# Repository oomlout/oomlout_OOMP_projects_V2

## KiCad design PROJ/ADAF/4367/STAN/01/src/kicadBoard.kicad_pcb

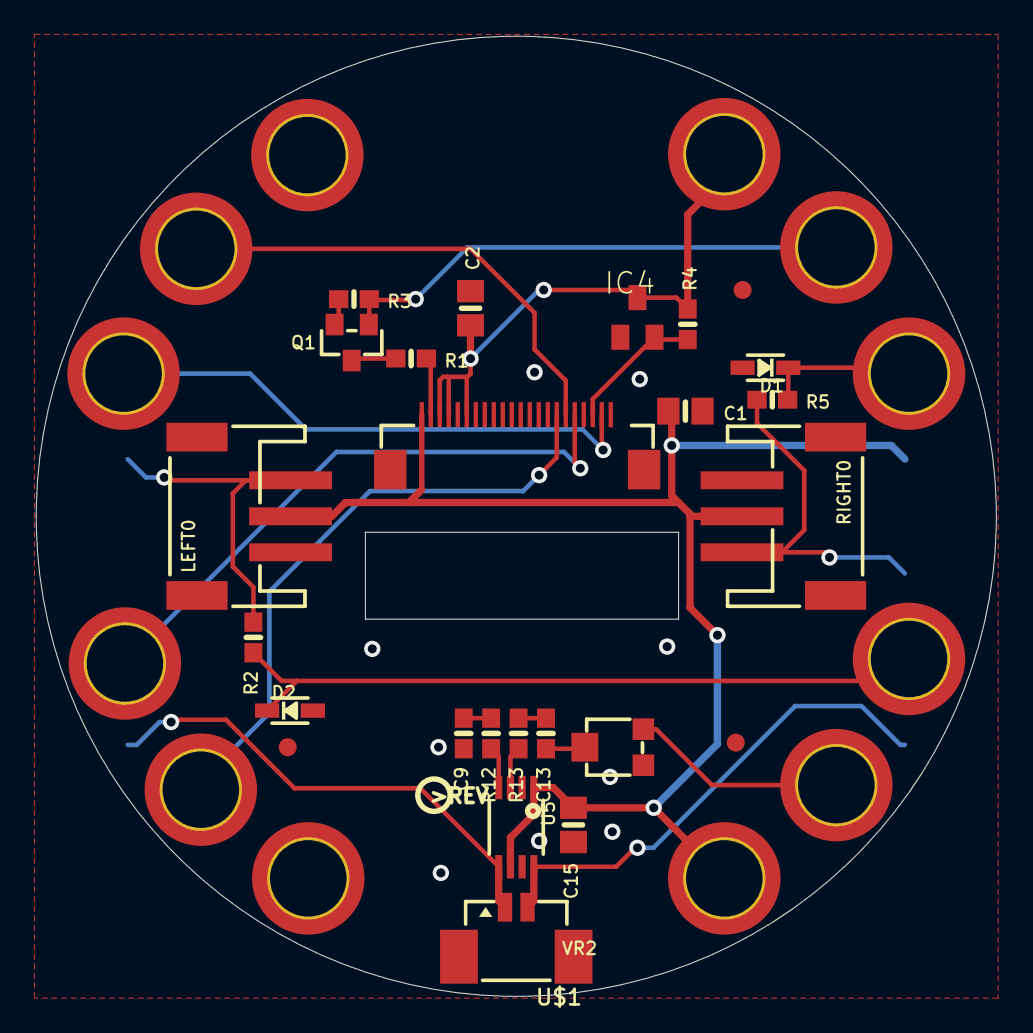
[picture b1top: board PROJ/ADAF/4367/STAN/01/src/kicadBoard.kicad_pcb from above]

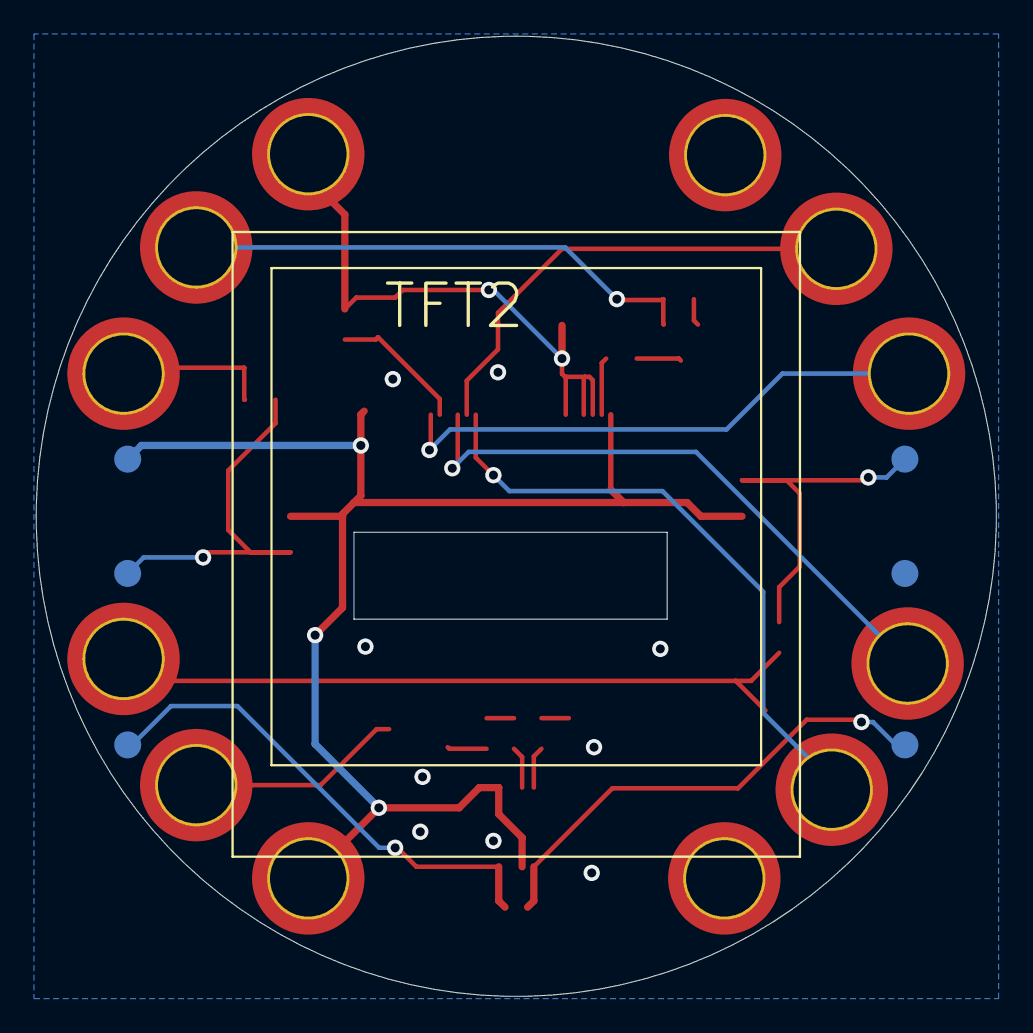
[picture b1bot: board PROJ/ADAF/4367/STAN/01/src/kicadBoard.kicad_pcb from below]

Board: 16 copper layers, 53.3 x 53.3 mm, 46 parts (8 on the bottom side), 23 nets.

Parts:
C1, C2, C15: 10uF; 0805-NO
C9, C13: 1uF; 0603-NO
D1, D2: 3.6V; SOD-323
IC4: APX803-SAG; SOT23
LEFT0: JST PH 3; JSTPH3
Q1: BSS138; SOT23-WIDE
R1: 33 ohm; 0603-NO
R2, R5: 1K; 0603-NO
R3, R4: 10K; 0603-NO
R12, R13: 100; 0603-NO
RIGHT0: JST PH 3; JSTPH3
TFT2: DISP_TFT_1.54IN_240X240_22P; TFT_1.54IN_240X240_22PIN
TP1, TP14, TP15, TP16, TP17, TP18: TESTPOINT_ROUND_1.5MM_NO
TP2, TP3, TP4, TP5, TP6, TP7, TP8, TP9, TP10, TP11, TP12, TP13: SEWTAP_SMTNUTM3; SMT_NUT_3MM
U5: PAM8302AASCR; MSOP8_0.65MM
U$1: CON_MOLEX_2P; 53398-0271
U$2, U$3, U$6: FIDUCIAL_1MM
U$7: PCBFEAT-REV-040
U$17: TFTGIZMO_FRONT
U$18: TFTGIZMO_BACK
VR2: 10K trim; TRIMPOT_BOURNS_3303W

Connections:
3.3V: C2.1, IC4.3, R4.2, TFT2.3, TFT2.4, TFT2.6, TP2.P$1
A0_SPEAKER: TP9.P$1, VR2.3
A1: D2.C, R2.2, TP8.P$1
A1_: LEFT0.3, R2.1, TP1.P$1
A2: D1.C, R5.2, TP7.P$1
A2_: R5.1, RIGHT0.3, TP14.P$1
A3_BACKLITE: Q1.1, R3.2, TP6.P$1
A6_CS: TFT2.18, TP12.P$1
A7_DC: TFT2.16, TP13.P$1
GND: C1.2, C2.2, C9.2, C15.2, D1.A, D2.A, IC4.1, LEFT0.1, Q1.2, R3.1, RIGHT0.1, TFT2.5, TFT2.7, TFT2.8, TFT2.9, TFT2.10, TFT2.11, TFT2.12, TFT2.13, TFT2.14, TFT2.15, TFT2.22, TFT2.SUPPORT1, TFT2.SUPPORT2, TP4.P$1, TP5.P$1, TP18.P$1, U5.7, VR2.1
LEDK: R1.2, TFT2.2
MOSI: TFT2.21, TP11.P$1
unnamed: Q1.3, R1.1
unnamed: R12.2, U5.4
unnamed: R13.2, U5.3
unnamed: C9.1, R12.1
unnamed: C13.1, R13.1
unnamed: C13.2, VR2.2
SCK: TFT2.17, TP10.P$1
SPKR+: TP15.P$1, U5.5, U$1.1
SPKR-: TP16.P$1, U5.8, U$1.2
V+: C1.1, C15.1, LEFT0.2, RIGHT0.2, TFT2.1, TP3.P$1, TP17.P$1, U5.1, U5.6
~TFT_RST: IC4.2, R4.1, TFT2.20

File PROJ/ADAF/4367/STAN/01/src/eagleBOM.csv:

"Part";"Value";"Device";"Package";"Description";"BOM";
"C1";"10uF";"CAP_CERAMIC0805-NOOUTLINE";"0805-NO";"Ceramic Capacitors";"";
"C2";"10uF";"CAP_CERAMIC0805-NOOUTLINE";"0805-NO";"Ceramic Capacitors";"";
"C9";"1uF";"CAP_CERAMIC0603_NO";"0603-NO";"Ceramic Capacitors";"";
"C13";"1uF";"CAP_CERAMIC0603_NO";"0603-NO";"Ceramic Capacitors";"";
"C15";"10uF";"CAP_CERAMIC0805-NOOUTLINE";"0805-NO";"Ceramic Capacitors";"";
"D1";"3.6V";"DIODE-ZENERSOD323";"SOD-323";"Zener Diode";"";
"D2";"3.6V";"DIODE-ZENERSOD323";"SOD-323";"Zener Diode";"";
"IC4";"APX803-SAG";"AXP083-SAG";"SOT23";"";"";
"LEFT";"JST PH 3";"CON_JST_PH_3PIN";"JSTPH3";"";"";
"Q1";"BSS138";"MOSFET-NWIDE";"SOT23-WIDE";"N-Channel Mosfet";"";
"R1";"33 ohm";"RESISTOR_0603_NOOUT";"0603-NO";"Resistors";"";
"R2";"1K";"RESISTOR_0603_NOOUT";"0603-NO";"Resistors";"";
"R3";"10K";"RESISTOR_0603_NOOUT";"0603-NO";"Resistors";"";
"R4";"10K";"RESISTOR_0603_NOOUT";"0603-NO";"Resistors";"";
"R5";"1K";"RESISTOR_0603_NOOUT";"0603-NO";"Resistors";"";
"R12";"100";"RESISTOR_0603_NOOUT";"0603-NO";"Resistors";"";
"R13";"100";"RESISTOR_0603_NOOUT";"0603-NO";"Resistors";"";
"RIGHT";"JST PH 3";"CON_JST_PH_3PIN";"JSTPH3";"";"";
"TFT2";"DISP_TFT_1.54IN_240X240_22P";"DISP_TFT_1.54IN_240X240_22P";"TFT_1.54IN_240X240_22PIN";"";"";
"TP1";"";"TESTPOINTROUND1.5MMNO";"TESTPOINT_ROUND_1.5MM_NO";"Test Point";"";
"TP2";"SEWTAP_SMTNUTM3";"SEWTAP_SMTNUTM3";"SMT_NUT_3MM";"";"";
"TP3";"SEWTAP_SMTNUTM3";"SEWTAP_SMTNUTM3";"SMT_NUT_3MM";"";"";
"TP4";"SEWTAP_SMTNUTM3";"SEWTAP_SMTNUTM3";"SMT_NUT_3MM";"";"";
"TP5";"SEWTAP_SMTNUTM3";"SEWTAP_SMTNUTM3";"SMT_NUT_3MM";"";"";
"TP6";"SEWTAP_SMTNUTM3";"SEWTAP_SMTNUTM3";"SMT_NUT_3MM";"";"";
"TP7";"SEWTAP_SMTNUTM3";"SEWTAP_SMTNUTM3";"SMT_NUT_3MM";"";"";
"TP8";"SEWTAP_SMTNUTM3";"SEWTAP_SMTNUTM3";"SMT_NUT_3MM";"";"";
"TP9";"SEWTAP_SMTNUTM3";"SEWTAP_SMTNUTM3";"SMT_NUT_3MM";"";"";
"TP10";"SEWTAP_SMTNUTM3";"SEWTAP_SMTNUTM3";"SMT_NUT_3MM";"";"";
"TP11";"SEWTAP_SMTNUTM3";"SEWTAP_SMTNUTM3";"SMT_NUT_3MM";"";"";
"TP12";"SEWTAP_SMTNUTM3";"SEWTAP_SMTNUTM3";"SMT_NUT_3MM";"";"";
"TP13";"SEWTAP_SMTNUTM3";"SEWTAP_SMTNUTM3";"SMT_NUT_3MM";"";"";
"TP14";"";"TESTPOINTROUND1.5MMNO";"TESTPOINT_ROUND_1.5MM_NO";"Test Point";"";
"TP15";"";"TESTPOINTROUND1.5MMNO";"TESTPOINT_ROUND_1.5MM_NO";"Test Point";"";
"TP16";"";"TESTPOINTROUND1.5MMNO";"TESTPOINT_ROUND_1.5MM_NO";"Test Point";"";
"TP17";"";"TESTPOINTROUND1.5MMNO";"TESTPOINT_ROUND_1.5MM_NO";"Test Point";"";
"TP18";"";"TESTPOINTROUND1.5MMNO";"TESTPOINT_ROUND_1.5MM_NO";"Test Point";"";
"U$1";"CON_MOLEX_2P";"CON_MOLEX_2P";"53398-0271";"";"";
"U$2";"FIDUCIAL_1MM";"FIDUCIAL_1MM";"FIDUCIAL_1MM";"Fiducial Alignment Points";"EXCLUDE";
"U$3";"FIDUCIAL_1MM";"FIDUCIAL_1MM";"FIDUCIAL_1MM";"Fiducial Alignment Points";"EXCLUDE";
"U$6";"FIDUCIAL_1MM";"FIDUCIAL_1MM";"FIDUCIAL_1MM";"Fiducial Alignment Points";"EXCLUDE";
"U5";"PAM8302AASCR";"AUDIOAMP_PAM8302A";"MSOP8_0.65MM";"PAM8302A - 2.5W Class-D Mono Audio Amplifier";"";
"VR2";"10K trim";"TRIMPOT3303W/X";"TRIMPOT_BOURNS_3303W";"3-Pin SMT Trimpots";"";

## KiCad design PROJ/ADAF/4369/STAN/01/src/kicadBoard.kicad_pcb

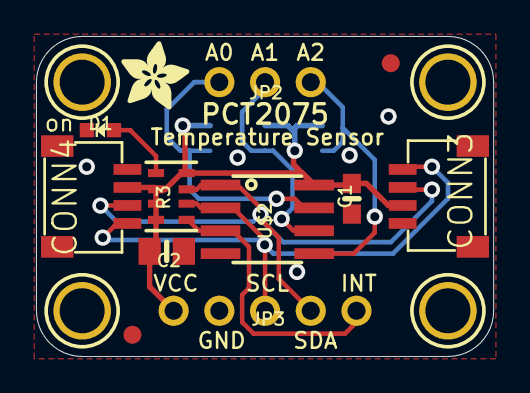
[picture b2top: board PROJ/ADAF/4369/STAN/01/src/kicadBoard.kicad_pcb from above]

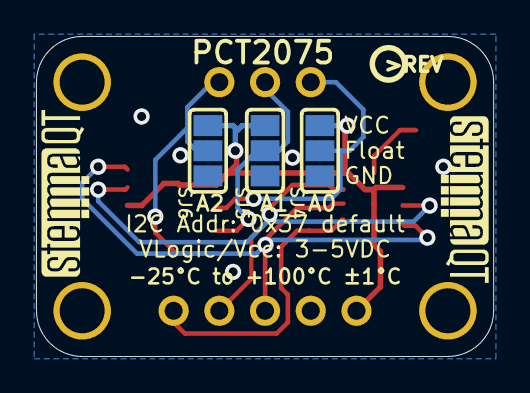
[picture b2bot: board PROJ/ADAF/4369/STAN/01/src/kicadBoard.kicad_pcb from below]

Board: 2 copper layers, 25.4 x 17.8 mm, 22 parts (6 on the bottom side), 9 nets.

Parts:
C1: 0.1uF; 0603-NO
C2: 10uF; 0805-NO
CONN3, CONN4: STEMMA_I2C_QT; JST_SH4
D1: GREEN; CHIPLED_0603_NOOUTLINE
FID3, FID4: FIDUCIAL_1MM
JP2: 1X03_ROUND
JP3: 1X05_ROUND
R3: 10K; RESPACK_4X0603
SJ4, SJ5, SJ6: SOLDERJUMPER_2WAY_OPEN_NOPASTE
U$1, U$17, U$19, U$21: MOUNTINGHOLE2.5; MOUNTINGHOLE_2.5_PLATED
U$2: PCT2075D; SOIC8_150MIL
U$22: ADAFRUIT_3.5MM
U$25: PCBFEAT-REV-040
U$30, U$31: STEMMAQT

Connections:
A0: JP2.1, SJ4.2, U$2.7
A1: JP2.2, SJ5.2, U$2.6
A2: JP2.3, SJ6.2, U$2.5
GND: C1.2, C2.2, CONN3.1, CONN4.1, D1.C, JP3.2, SJ4.1, SJ5.1, SJ6.1, U$2.4
INT: JP3.5, R3.5, U$2.3
unnamed: D1.A, R3.1
SCL: CONN3.4, CONN4.4, JP3.3, R3.6, U$2.2
SDA: CONN3.3, CONN4.3, JP3.4, R3.7, U$2.1
VCC: C1.1, C2.1, CONN3.2, CONN4.2, JP3.1, R3.2, R3.3, R3.4, R3.8, SJ4.3, SJ5.3, SJ6.3, U$2.8

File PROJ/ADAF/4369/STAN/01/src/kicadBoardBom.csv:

"Id";"Designator";"Package";"Quantity";"Designation";"Supplier and ref";
1;"U$19,U$1,U$21,U$17";"MOUNTINGHOLE_2.5_PLATED";4;"MOUNTINGHOLE2.5";;;
2;"JP2";"1X03_ROUND";1;"";;;
3;"FID3,FID4";"FIDUCIAL_1MM";2;"FIDUCIAL_1MM";;;
4;"CONN3,CONN4";"JST_SH4";2;"STEMMA_I2C_QT";;;
5;"R3";"RESPACK_4X0603";1;"10K";;;
6;"U$2";"SOIC8_150MIL";1;"PCT2075D";;;
7;"D1";"CHIPLED_0603_NOOUTLINE";1;"GREEN";;;
8;"U$22";"ADAFRUIT_3.5MM";1;"";;;
9;"C1";"0603-NO";1;"0.1uF";;;
10;"C2";"0805-NO";1;"10uF";;;
11;"JP3";"1X05_ROUND";1;"";;;
12;"SJ6,SJ4,SJ5";"SOLDERJUMPER_2WAY_OPEN_NOPASTE";3;"";;;
13;"U$25";"PCBFEAT-REV-040";1;"";;;
14;"U$31,U$30";"STEMMAQT";2;"";;;

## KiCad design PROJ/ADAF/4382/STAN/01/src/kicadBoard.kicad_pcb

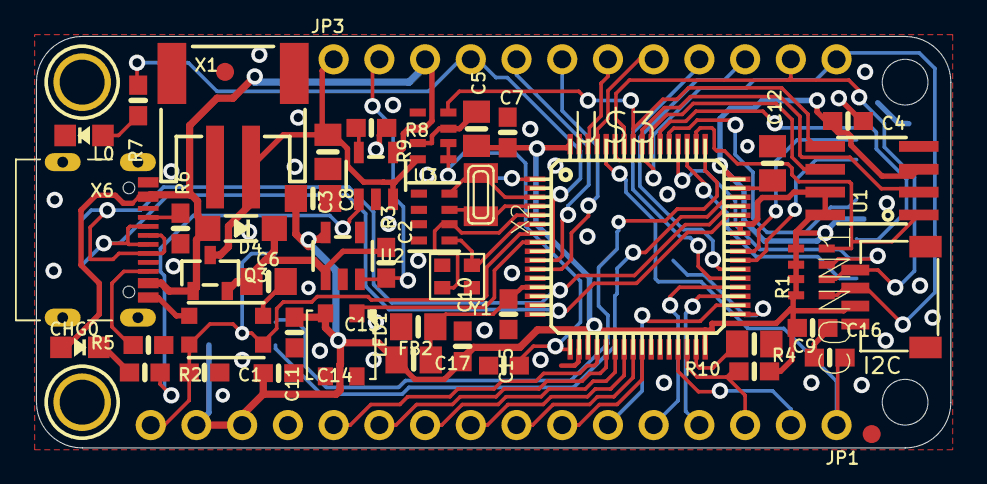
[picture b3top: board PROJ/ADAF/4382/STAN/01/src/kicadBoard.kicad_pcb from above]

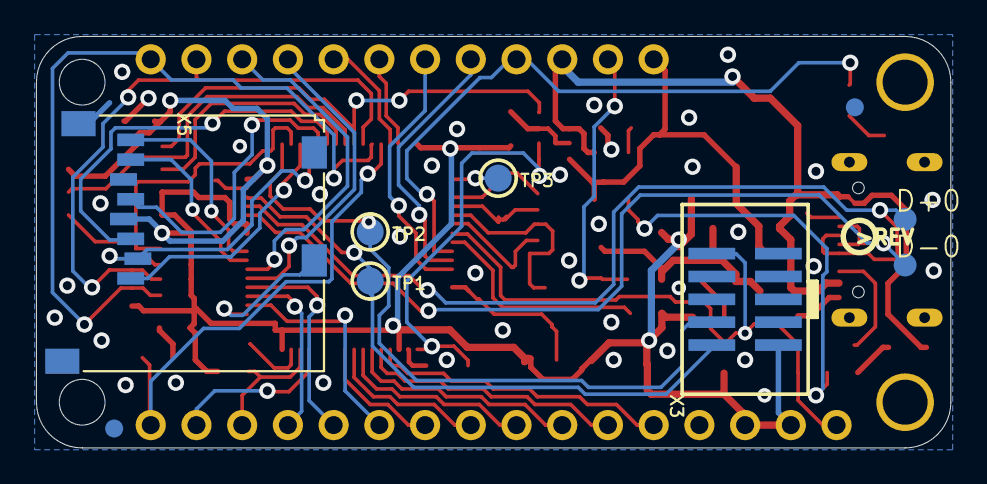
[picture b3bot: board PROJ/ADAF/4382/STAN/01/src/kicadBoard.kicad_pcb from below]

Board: 2 copper layers, 50.8 x 22.9 mm, 63 parts (11 on the bottom side), 59 nets.

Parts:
@HOLE0, @HOLE1: (no value)
C1, C15: 0.1uF; 0603-NO
C2: 22pF; RESPACK_4X0603
C3, C6, C8, C9, C12, C13: 10µF; 0805-NO
C4, C7, C10, C11, C14, C16, C17: 1uF; 0603-NO
C5: 10uF; 0805-NO
CHG0: ORANGE; CHIPLED_0805_NOOUTLINE
CONN1: STEMMA_I2C_QT; JST_SH4
D4: MBR054; SOD-123
D+0: TPB1,27; B1,27
D-0: TPB1,27; B1,27
FB2: ferrite; 0805-NO
JP1: 1X16_ROUND
JP3: 1X12_ROUND
L0: RED; CHIPLED_0805_NOOUTLINE
LED1: WS2812B3535; LED3535
Q3: DMG3405; SOT23-R
R1: 10K; RESPACK_4X0603_NO
R2: 1K; 0603-NO
R3: 10K; 0603-NO
R4, R10: 100K; 0603-NO
R5, R6, R8: 5.1K; 0603-NO
R7: 2.2K; 0603-NO
R9: 100K; RESPACK_4X0603_NO
SW1: KMR2; BTN_KMR2_4.6X2.8
TP1, TP2, TP3: TESTPOINT_ROUND_1.5MM
U1: 25Q16; SOIC8_150MIL
U2: AP2112-3.3; SOT23-5
U3: MCP73831T-2ACI/OT; SOT23-5
U$3: STM32F405R; TQFP64
U$5, U$34, U$35, U$37: FIDUCIAL_1MM
U$13: PCBFEAT-REV-040
U$24: FEATHER_STM32F405_TOP
U$31, U$32: MOUNTINGHOLE2.5; MOUNTINGHOLE_2.5_PLATED
U$40: FEATHER_STM32F405_BOT
X1: JSTPH; JSTPH2
X2: 32.768; XTAL3215
X3: 2X05_1.27MM_SMT
X5: MICROSD
X6: USB_C_CUSB31-CFM2AX-01-X
Y1: 12mhz; CRYSTAL_2.5X2

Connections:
+3V3: C4.1, C5.1, C7.1, C8.1, C10.1, C11.1, C14.1, C16.1, CONN1.2, FB2.1, JP1.14, JP1.15, LED1.2, R1.5, R1.6, R1.7, R1.8, R10.1, U1.3, U1.7, U1.8, U2.5, U$3.19, U$3.32, U$3.42, U$3.43, U$3.48, U$3.64, X3.1, X5.4
A0: JP1.12, U$3.20
A1: JP1.11, U$3.21
A2: JP1.10, U$3.22
A3: JP1.9, U$3.23
A4: JP1.8, U$3.24
A5: JP1.7, U$3.25
AVCC: C13.1, C15.1, FB2.2, U$3.13
BATTERY: TP3.P$1, U$3.1
BOOT0: JP1.1, R4.1, U$3.60
CC1: R6.2, X6.A5
CC2: R5.2, X6.B5
D5: JP3.10, U$3.38
D6: JP3.9, U$3.37
D8_NEOPIX: LED1.1, U$3.8
D9: JP3.8, U$3.61
D10: JP3.7, U$3.62
D11: JP3.6, U$3.11
D12: JP3.5, U$3.10
D13: JP3.4, R7.1, U$3.9
D+: D+0.TP, U$3.45, X6.A6, X6.B6
D-: D-0.TP, U$3.44, X6.A7, X6.B7
EN: JP3.2, R3.1, U2.3
FLASH_CS: R1.4, U1.1, U$3.50
FLASH_MISO: U1.2, U$3.56
FLASH_MOSI: R9.4, U1.5, U$3.57
FLASH_SCK: U1.6, U$3.55
GND: C1.2, C2.5, C2.6, C2.7, C2.8, C3.2, C4.2, C5.2, C6.2, C7.2, C8.2, C9.2, C10.2, C11.2, C12.2, C13.2, C14.2, C15.2, C16.2, C17.2, CONN1.1, CONN1.MT1, CONN1.MT2, JP1.13, L0.C, LED1.4, R4.2, R5.1, R6.1, R8.2, R9.3, R9.5, R9.7, SW1.B, SW1.B', U1.4, U2.2, U3.2, U$3.12, U$3.18, U$3.28, U$3.63, X1.1, X3.3, X3.5, X3.7, X3.9, X5.6, X5.CD1, X5.MT1, X5.MT2, X6.A1B12, X6.B1A12
MISO: JP1.4, U$3.35
MOSI: JP1.5, U$3.36
unnamed: CHG0.C, R2.1
unnamed: L0.A, R7.2
unnamed: R2.2, U3.1
unnamed: R8.1, U3.5
unnamed: C2.4, U$3.3, X2.P$1
unnamed: C2.2, U$3.5, Y1.3
unnamed: C2.3, U$3.4, X2.P$2
unnamed: C2.1, U$3.6, Y1.1
RX_D0: JP1.3, R10.2, U$3.30
SCK: JP1.6, U$3.34
SCL: CONN1.4, JP3.11, R1.2, U$3.58
SDA: CONN1.3, JP3.12, R1.1, U$3.59
SDIO_CLK: U$3.53, X5.5
SDIO_CMD: U$3.54, X5.3
SDIO_D0: U$3.39, X5.7
SDIO_D1: U$3.40, X5.8
SDIO_D2: U$3.51, X5.1
SDIO_D3: R1.3, U$3.52, X5.2
SD_DETECT: U$3.33, X5.CD2
SWCLK: TP2.P$1, U$3.49, X3.4
SWDIO: TP1.P$1, U$3.46, X3.2
TX_D1: JP1.2, U$3.29
VBAT: C3.1, JP3.1, Q3.3, R9.8, U3.3, X1.2
VBUS: CHG0.A, D4.A, JP3.3, Q3.1, R9.6, U3.4, X6.A4B9, X6.B4A9
VCAP1: C9.1, U$3.31
VCAP2: C12.1, U$3.47
VHI: C6.1, D4.C, Q3.2, R3.2, U2.1
V_DIV: C17.1, R9.1, R9.2, U$3.17
~RESET: C1.1, JP1.16, SW1.A, SW1.A', U$3.7, X3.10

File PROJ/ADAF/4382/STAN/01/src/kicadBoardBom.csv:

"Id";"Designator";"Package";"Quantity";"Designation";"Supplier and ref";
1;"C6,C12,C9,C3,C8,C13";"0805-NO";6;"10µF";;;
2;"L0";"CHIPLED_0805_NOOUTLINE";1;"RED";;;
3;"R8,R6,R5";"0603-NO";3;"5.1K";;;
4;"U$35,U$34,U$5,U$37";"FIDUCIAL_1MM";4;"FIDUCIAL_1MM";;;
5;"C4,C7,C11,C10,C17,C14,C16";"0603-NO";7;"1uF";;;
6;"Y1";"CRYSTAL_2.5X2";1;"12mhz";;;
7;"R7";"0603-NO";1;"2.2K";;;
8;"CHG0";"CHIPLED_0805_NOOUTLINE";1;"ORANGE";;;
9;"X2";"XTAL3215";1;"32.768";;;
10;"R10,R4";"0603-NO";2;"100K";;;
11;"U$3";"TQFP64";1;"STM32F405R";;;
12;"R3";"0603-NO";1;"10K";;;
13;"R2";"0603-NO";1;"1K";;;
14;"U$31,U$32";"MOUNTINGHOLE_2.5_PLATED";2;"MOUNTINGHOLE2.5";;;
15;"D4";"SOD-123";1;"MBR054";;;
16;"SW1";"BTN_KMR2_4.6X2.8";1;"KMR2";;;
17;"U$24";"FEATHER_STM32F405_TOP";1;"";;;
18;"@HOLE0,@HOLE1";"";2;"";;;
19;"U3";"SOT23-5";1;"MCP73831T-2ACI/OT";;;
20;"C15,C1";"0603-NO";2;"0.1uF";;;
21;"R9";"RESPACK_4X0603_NO";1;"100K";;;
22;"U2";"SOT23-5";1;"AP2112-3.3";;;
23;"FB2";"0805-NO";1;"ferrite";;;
24;"LED1";"LED3535";1;"WS2812B3535";;;
25;"R1";"RESPACK_4X0603_NO";1;"10K";;;
26;"U1";"SOIC8_150MIL";1;"25Q16";;;
27;"X6";"USB_C_CUSB31-CFM2AX-01-X";1;"";;;
28;"C5";"0805-NO";1;"10uF";;;
29;"X1";"JSTPH2";1;"JSTPH";;;
30;"JP3";"1X12_ROUND";1;"";;;
31;"C2";"RESPACK_4X0603";1;"22pF";;;
32;"CONN1";"JST_SH4";1;"STEMMA_I2C_QT";;;
33;"JP1";"1X16_ROUND";1;"";;;
34;"Q3";"SOT23-R";1;"DMG3405";;;
35;"X5";"MICROSD";1;"";;;
36;"TP3,TP1,TP2";"TESTPOINT_ROUND_1.5MM";3;"";;;
37;"D+0,D-0";"B1,27";2;"TPB1,27";;;
38;"X3";"2X05_1.27MM_SMT";1;"";;;
39;"U$13";"PCBFEAT-REV-040";1;"";;;
40;"U$40";"FEATHER_STM32F405_BOT";1;"";;;

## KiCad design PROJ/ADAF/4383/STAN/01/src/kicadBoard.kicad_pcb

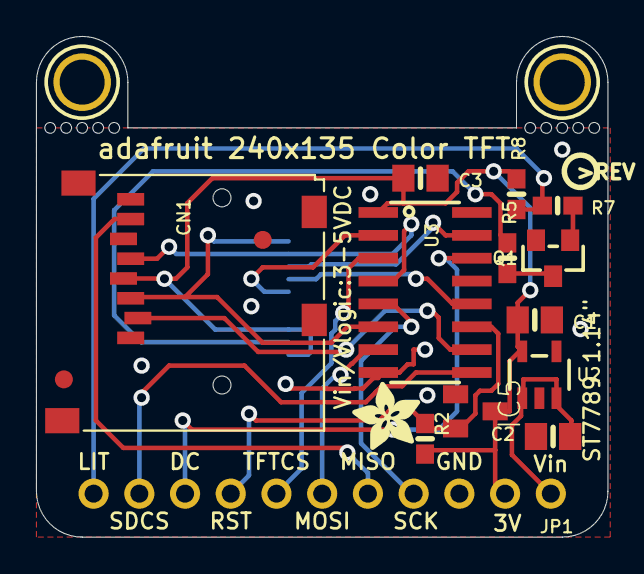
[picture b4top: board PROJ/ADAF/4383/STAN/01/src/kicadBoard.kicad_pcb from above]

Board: 2 copper layers, 31.8 x 27.8 mm, 30 parts (1 on the bottom side), 20 nets.

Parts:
@HOLE0, @HOLE1, @HOLE2, @HOLE3, @HOLE4, @HOLE5, @HOLE6, @HOLE7, @HOLE8, @HOLE9: (no value)
C1, C2: 10µF; 0805-NO
C3: 0.1uF; 0805-NO
CN1: MICROSD
DISP1: DISP_LCD_GENERIC_SPI_1.14IN_240X135_WRAPUNDER; TFT_1.14IN_240X135_WRAPUNDER
FID1, FID2: FIDUCIAL_1MM
IC5: APX803; SOT23
JP1: 1X11_ROUND
Q1: MMBT2222; SOT23-WIDE
R2, R8: 10K; 0603-NO
R5: 22; 0603-NO
R7: 1K; 0603-NO
U2: MIC5225-3.3; SOT23-5
U3: 74HC4050D; SOIC16
U$4: MICROSD; ADAFRUIT_3.5MM
U$6: PCBFEAT-REV-040
U$9, U$10: MOUNTINGHOLE2.5; MOUNTINGHOLE_2.5_PLATED

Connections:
3.3V: C1.1, C3.1, CN1.4, DISP1.10, DISP1.12, IC5.3, JP1.2, R2.2, R8.2, U2.5, U3.1
BACKLIGHT: JP1.11, R7.1, R8.1
DC: JP1.9, U3.14
DC_3V: DISP1.5, U3.15
GND: C1.2, C2.2, C3.2, CN1.6, CN1.MT1, CN1.MT2, DISP1.8, DISP1.13, IC5.1, JP1.3, Q1.2, U2.2, U3.8
LED_K: DISP1.11, R5.2
MISO_3V: CN1.7, JP1.5
MOSI: JP1.6, U3.7
MOSI_3V: CN1.3, DISP1.3, U3.6
unnamed: Q1.1, R7.2
unnamed: Q1.3, R5.1
SCK: JP1.4, U3.5
SCK_3V: CN1.5, DISP1.4, U3.4
SDCS: JP1.10, U3.9
SDCS_3V: CN1.2, U3.10
TFTCS: JP1.7, U3.3
TFTCS_3V: DISP1.7, U3.2
VIN: C2.1, JP1.1, U2.1, U2.3
~TFTRST_3V: DISP1.6, U3.12
~TFTRST: IC5.2, JP1.8, R2.1, U3.11

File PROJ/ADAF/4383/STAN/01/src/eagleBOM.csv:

"Part";"Value";"Device";"Package";"Description";"BOM";
"C1";"10µF";"CAP_CERAMIC0805-NOOUTLINE";"0805-NO";"Ceramic Capacitors";"";
"C2";"10µF";"CAP_CERAMIC0805-NOOUTLINE";"0805-NO";"Ceramic Capacitors";"";
"C3";"0.1uF";"CAP_CERAMIC0805-NOOUTLINE";"0805-NO";"Ceramic Capacitors";"";
"CN1";"";"MICROSD";"MICROSD";"MicroSD/Transflash Card Holder with SPI pinout";"";
"DISP1";"DISP_LCD_GENERIC_SPI_1.14IN_240X135_WRAPUNDER";"DISP_LCD_GENERIC_SPI_1.14IN_240X135_WRAPUNDER";"TFT_1.14IN_240X135_WRAPUNDER";"";"";
"FID1";"FIDUCIAL_1MM";"FIDUCIAL_1MM";"FIDUCIAL_1MM";"Fiducial Alignment Points";"EXCLUDE";
"FID2";"FIDUCIAL_1MM";"FIDUCIAL_1MM";"FIDUCIAL_1MM";"Fiducial Alignment Points";"EXCLUDE";
"IC5";"APX803";"AXP083-SAG";"SOT23";"";"";
"JP1";"";"HEADER-1X11";"1X11_ROUND";"";"";
"Q1";"MMBT2222";"TRANSISTOR_NPNWIDE";"SOT23-WIDE";"NPN Transistor";"";
"R2";"10K";"RESISTOR_0603_NOOUT";"0603-NO";"Resistors";"";
"R5";"22";"RESISTOR_0603_NOOUT";"0603-NO";"Resistors";"";
"R7";"1K";"RESISTOR_0603_NOOUT";"0603-NO";"Resistors";"";
"R8";"10K";"RESISTOR_0603_NOOUT";"0603-NO";"Resistors";"";
"U$9";"MOUNTINGHOLE2.5";"MOUNTINGHOLE2.5";"MOUNTINGHOLE_2.5_PLATED";"Mounting Hole";"EXCLUDE";
"U$10";"MOUNTINGHOLE2.5";"MOUNTINGHOLE2.5";"MOUNTINGHOLE_2.5_PLATED";"Mounting Hole";"EXCLUDE";
"U2";"MIC5225-3.3";"VREG_SOT23-5";"SOT23-5";"SOT23-5 Fixed Voltage Regulators";"";
"U3";"74HC4050D";"74HC4050D";"SOIC16";"6-channel level shifter";"";

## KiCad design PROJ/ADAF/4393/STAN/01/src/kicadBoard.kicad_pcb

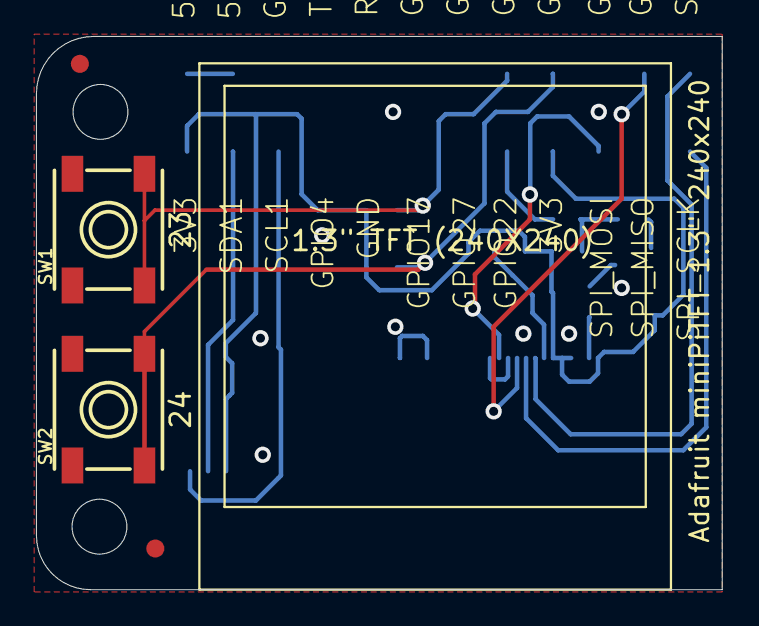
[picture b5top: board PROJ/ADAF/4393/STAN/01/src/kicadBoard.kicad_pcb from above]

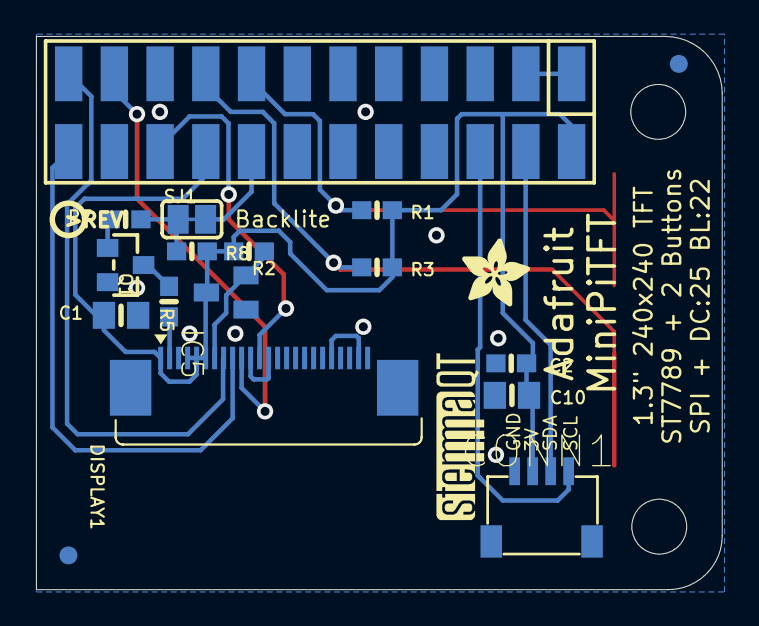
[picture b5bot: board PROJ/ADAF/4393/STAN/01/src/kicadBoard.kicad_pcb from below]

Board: 2 copper layers, 38.1 x 30.7 mm, 26 parts (19 on the bottom side), 17 nets.

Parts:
@HOLE0, @HOLE1: (no value)
C1, C10: 10uF; 0805-NO
C2: 1uF; 0603-NO
CONN1: STEMMA_I2C_QT; JST_SH4
DISPLAY1: DISP_LCD_ST7789_1.3IN; TFT_1.3IN_240X240_24P
FID1, FID2, FID3, FID4: FIDUCIAL_1MM
IC5: APX803; SOT23
Q1: MMBT2222; SOT23-WIDE
R1, R2, R3, R8: 10K; 0603-NO
R5: 10; 0603-NO
R7: 1K; 0603-NO
RASPI1: RASPBERRYPI_2X12_SMT
SJ1: SOLDERJUMPER_CLOSEDWIRE
SW1, SW2: EVQ-Q2_SMALLER
U$4: MICROSD; ADAFRUIT_3.5MM
U$6: PCBFEAT-REV-040
U$15: STEMMAQT

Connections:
3.3V: C1.2, C2.2, C10.2, CONN1.2, DISPLAY1.1, DISPLAY1.4, DISPLAY1.5, DISPLAY1.6, IC5.3, R1.2, R2.2, R3.2, R8.2, RASPI1.S1, RASPI1.S17
5.0V: RASPI1.S2, RASPI1.S4
BACKLIGHT: R7.1, R8.1, SJ1.1
BUTTONA: R1.1, RASPI1.S16, SW1.A, SW1.A'
BUTTONB: R3.1, RASPI1.S18, SW2.A, SW2.A'
GND: C1.1, C2.1, C10.1, CONN1.1, DISPLAY1.3, DISPLAY1.11, DISPLAY1.13, DISPLAY1.14, DISPLAY1.15, DISPLAY1.16, DISPLAY1.17, DISPLAY1.18, DISPLAY1.19, DISPLAY1.20, DISPLAY1.23, DISPLAY1.24, IC5.1, Q1.2, RASPI1.S6, RASPI1.S9, RASPI1.S14, RASPI1.S20, SW1.B, SW1.B', SW2.B, SW2.B'
GPIO22: RASPI1.S15, SJ1.2
LED_K: DISPLAY1.2, R5.2
MOSI: DISPLAY1.12, RASPI1.S19
unnamed: Q1.1, R7.2
unnamed: Q1.3, R5.1
SCL: CONN1.4, RASPI1.S5
SCLK: DISPLAY1.9, RASPI1.S23
SDA: CONN1.3, RASPI1.S3
TFT_CS: DISPLAY1.8, RASPI1.S24
TFT_DC: DISPLAY1.10, RASPI1.S22
TFT_RST: DISPLAY1.7, IC5.2, R2.1

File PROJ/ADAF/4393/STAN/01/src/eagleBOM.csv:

"Part";"Value";"Device";"Package";"Description";"BOM";
"C1";"10uF";"CAP_CERAMIC0805-NOOUTLINE";"0805-NO";"Ceramic Capacitors";"";
"C2";"1uF";"CAP_CERAMIC0603_NO";"0603-NO";"Ceramic Capacitors";"";
"C10";"10uF";"CAP_CERAMIC0805-NOOUTLINE";"0805-NO";"Ceramic Capacitors";"";
"CONN1";"STEMMA_I2C_QT";"STEMMA_I2C_QT";"JST_SH4";"";"";
"DISPLAY1";"DISP_LCD_ST7789_1.3IN";"DISP_LCD_ST7789_1.3IN";"TFT_1.3IN_240X240_24P";"";"";
"FID1";"FIDUCIAL_1MM";"FIDUCIAL_1MM";"FIDUCIAL_1MM";"Fiducial Alignment Points";"EXCLUDE";
"FID2";"FIDUCIAL_1MM";"FIDUCIAL_1MM";"FIDUCIAL_1MM";"Fiducial Alignment Points";"EXCLUDE";
"FID3";"FIDUCIAL_1MM";"FIDUCIAL_1MM";"FIDUCIAL_1MM";"Fiducial Alignment Points";"EXCLUDE";
"FID4";"FIDUCIAL_1MM";"FIDUCIAL_1MM";"FIDUCIAL_1MM";"Fiducial Alignment Points";"EXCLUDE";
"IC5";"APX803";"AXP083-SAG";"SOT23";"";"";
"Q1";"MMBT2222";"TRANSISTOR_NPNWIDE";"SOT23-WIDE";"NPN Transistor";"";
"R1";"10K";"RESISTOR_0603_NOOUT";"0603-NO";"Resistors";"";
"R2";"10K";"RESISTOR_0603_NOOUT";"0603-NO";"Resistors";"";
"R3";"10K";"RESISTOR_0603_NOOUT";"0603-NO";"Resistors";"";
"R5";"10";"RESISTOR_0603_NOOUT";"0603-NO";"Resistors";"";
"R7";"1K";"RESISTOR_0603_NOOUT";"0603-NO";"Resistors";"";
"R8";"10K";"RESISTOR_0603_NOOUT";"0603-NO";"Resistors";"";
"RASPI1";"RASPBERRYPI_2X12_SMT";"RASPBERRYPI_2X12_SMT";"RASPBERRYPI_2X12_SMT";"";"";
"SJ1";"";"SOLDERJUMPER_CLOSED";"SOLDERJUMPER_CLOSEDWIRE";"Solder Jumper - Closed";"";
"SW1";"";"SWITCH_TACT_SMT_EVQQ2_SMALL";"EVQ-Q2_SMALLER";"SMT Tact Switches";"";
"SW2";"";"SWITCH_TACT_SMT_EVQQ2_SMALL";"EVQ-Q2_SMALLER";"SMT Tact Switches";"";

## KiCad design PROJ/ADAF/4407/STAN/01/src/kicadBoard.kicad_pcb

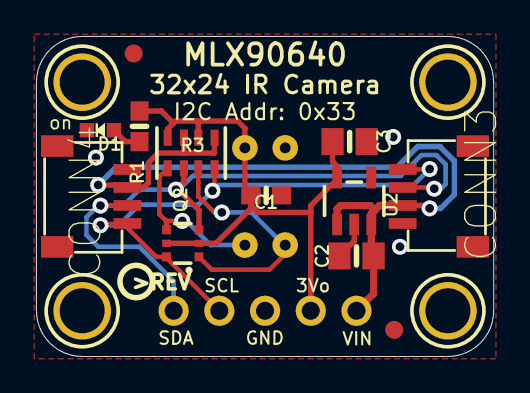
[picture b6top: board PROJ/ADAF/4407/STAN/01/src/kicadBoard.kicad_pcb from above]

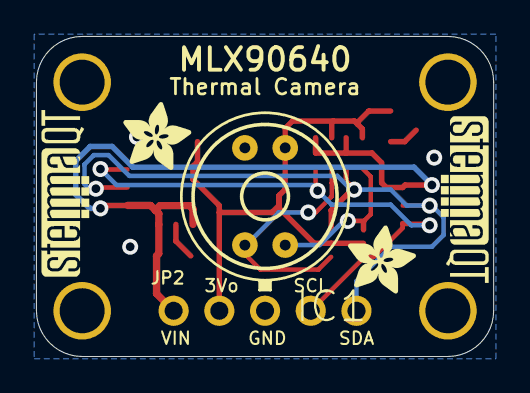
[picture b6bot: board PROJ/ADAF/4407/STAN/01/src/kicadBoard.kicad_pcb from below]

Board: 2 copper layers, 25.4 x 17.8 mm, 23 parts (6 on the bottom side), 8 nets.

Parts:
C1: 0.1uF; 0603-NO
C2, C3: 10uF; 0805-NO
CONN3, CONN4: STEMMA_I2C_QT; JST_SH4
D1: GREEN; CHIPLED_0603_NOOUTLINE
FID3, FID4: FIDUCIAL_1MM
IC1: MLX90640
JP2: 1X05_ROUND
Q2: BSS138; SOT363
R1: 10K; 0603-NO
R3: 4.7K; RESPACK_4X0603
U2: AP2112K-3.3; SOT23-5
U$1, U$17, U$19, U$21: MOUNTINGHOLE2.5; MOUNTINGHOLE_2.5_PLATED
U$4, U$22: ADAFRUIT_3.5MM
U$25: PCBFEAT-REV-040
U$30, U$31: STEMMAQT

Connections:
3.3V: C1.1, C3.1, IC1.VDD, JP2.2, Q2.2, Q2.5, R1.1, R3.2, R3.4, U2.5
GND: C1.2, C2.2, C3.2, CONN3.1, CONN4.1, D1.C, IC1.GND, JP2.3, U2.2
unnamed: D1.A, R1.2
SCL: CONN3.4, CONN4.4, JP2.4, Q2.6, R3.8
SCL_3V: IC1.SCL, Q2.1, R3.7
SDA: CONN3.3, CONN4.3, JP2.5, Q2.3, R3.6
SDA_3V: IC1.SDA, Q2.4, R3.5
VCC: C2.1, CONN3.2, CONN4.2, JP2.1, R3.1, R3.3, U2.1, U2.3

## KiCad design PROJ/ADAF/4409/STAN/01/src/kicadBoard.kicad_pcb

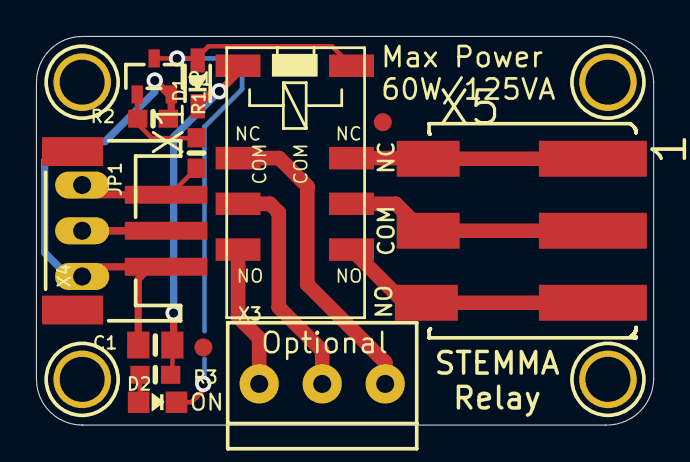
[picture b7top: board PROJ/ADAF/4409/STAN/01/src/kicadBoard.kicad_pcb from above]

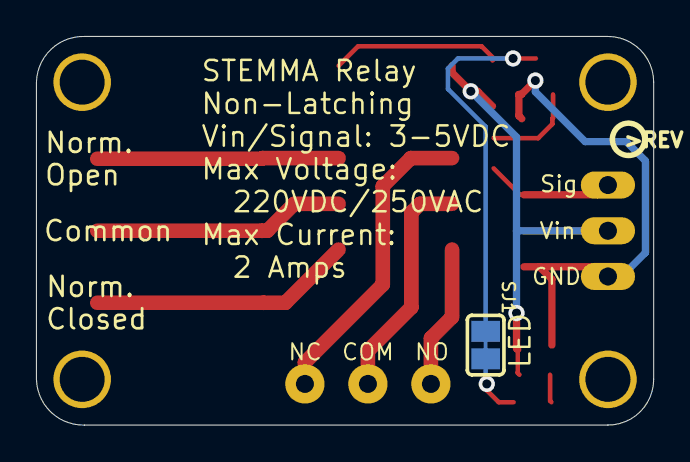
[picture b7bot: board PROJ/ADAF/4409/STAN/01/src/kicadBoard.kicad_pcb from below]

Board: 16 copper layers, 34.3 x 21.6 mm, 20 parts (2 on the bottom side), 13 nets.

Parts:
C1: 10uF; 0805-NO
D1: 1N4148; SOD-323
D2: RED; CHIPLED_0805_NOOUTLINE
FID2, FID3: FIDUCIAL_1MM
JP1: 0.1" Header; 1X03_OVAL
Q1: MMBT2222; SOT23-R
R1, R3: 1K; 0603-NO
R2: 10K; 0603-NO
SJ1: SOLDERJUMPER_CLOSEDWIRE
U$1, U$8, U$9, U$10: MOUNTINGHOLE2.5; MOUNTINGHOLE_2.5_PLATED
U$5: PCBFEAT-REV-040
X1: RELAY_NONLATCHING-EE2NUH; RELAY_EE2_NOLATCH
X3: 3.5mm Terminal; TERMBLOCK_1X3-3.5MM
X4: JST PH 3; JSTPH3
X5: 2060-403/998-404; P-2060-403_998-404

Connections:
COM: X1.9, X5.L2.1, X5.L2.2
GND: C1.2, JP1.3, Q1.2, R2.1, X4.1
unnamed: D1.A, Q1.3, SJ1.1, X1.12
unnamed: X1.3, X3.1
unnamed: X1.4, X3.2
unnamed: X1.5, X3.3
unnamed: Q1.1, R1.2, R2.2
unnamed: D2.C, SJ1.2
unnamed: D2.A, R3.1
NC: X1.10, X5.L1.1, X5.L1.2
NO: X1.8, X5.L3.1, X5.L3.2
SIGNAL: JP1.1, R1.1, X4.3
VIN: C1.1, D1.C, JP1.2, R3.2, X1.1, X4.2

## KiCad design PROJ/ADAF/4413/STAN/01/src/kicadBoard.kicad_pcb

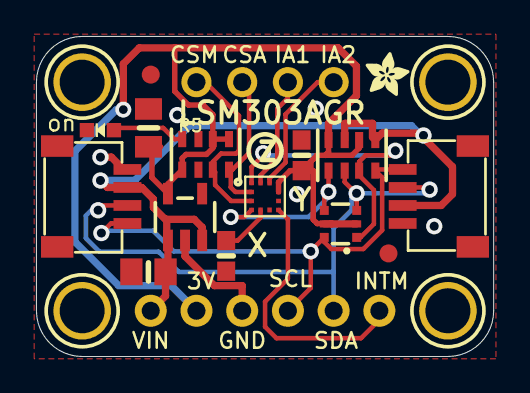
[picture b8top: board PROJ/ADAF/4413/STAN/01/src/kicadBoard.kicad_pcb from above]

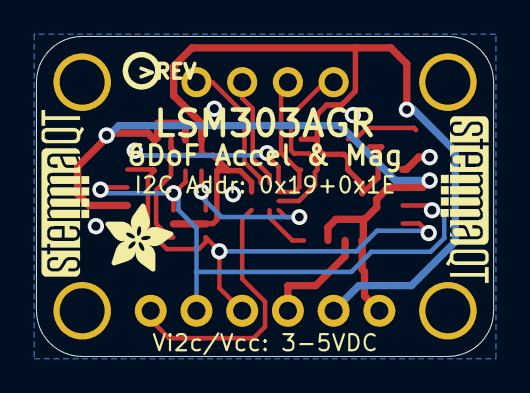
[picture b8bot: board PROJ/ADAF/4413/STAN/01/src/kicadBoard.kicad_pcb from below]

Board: 2 copper layers, 25.4 x 17.8 mm, 25 parts (4 on the bottom side), 14 nets.

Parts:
C1: 0.1uF; 0603-NO@1
C2: 10uF; 0805-NO
C3: 10uF; 0805_10MGAP
C4: 220nF; 0603-NO@1
CONN3, CONN4: STEMMA_I2C_QT; JST_SH4
D1: GREEN; CHIPLED_0603_NOOUTLINE
FID3, FID4: FIDUCIAL_1MM
JP1: 1X06_ROUND_70
JP3: 1X04_ROUND
Q2: BSS138; SOT363
R3, R5: 10K; RESPACK_4X0603
U2: AP2112K-3.3; SOT23-5
U$1, U$17, U$19, U$21: MOUNTINGHOLE2.5; MOUNTINGHOLE_2.5_PLATED
U$2: LSM303AGR; LGA12_2X2MM
U$20: ADAFRUIT_3.5MM
U$25: PCBFEAT-REV-040
U$30, U$31: STEMMAQT
U$40: ADAFRUIT_2.5MM

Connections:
3.3V: C1.1, C3.1, JP1.2, Q2.2, Q2.5, R3.2, R3.4, R5.1, R5.5, R5.6, U2.5, U$2.9, U$2.10
CS_ACCEL: JP3.2, R5.4, U$2.2
CS_MAG: JP3.1, R5.3, U$2.3
GND: C1.2, C2.2, C3.2, C4.2, CONN3.1, CONN4.1, D1.C, JP1.3, U2.2, U$2.6, U$2.8
INT1A_3V: JP3.3, U$2.12
INT2A_3V: JP3.4, U$2.11
INTM_3V: JP1.6, U$2.7
unnamed: D1.A, R5.8
unnamed: C4.1, U$2.5
SCL: CONN3.4, CONN4.4, JP1.4, Q2.6, R3.8
SCL_3V: Q2.1, R3.7, U$2.1
SDA: CONN3.3, CONN4.3, JP1.5, Q2.3, R3.6
SDA_3V: Q2.4, R3.5, U$2.4
VCC: C2.1, CONN3.2, CONN4.2, JP1.1, R3.1, R3.3, U2.1, U2.3
